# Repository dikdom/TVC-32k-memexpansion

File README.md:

# TVC 32k extender

## Magyar
Ez a repó Videoton TVC 32k bővítő modul terveit tartalmazza. A bővítőmodul arra való, hogy a 32k TVC gép memóriáját +32kB-al, 64k-ra bővítse. 64kB-os TVC gépek memóriáját nem változtatja.

Lehet rá egy LED-et is tenni, de nem muszáj.

Sőt, ha szeretsz tákolni, akkor azt is lehet, hogy ezen a kártyán legyen a TVC új reset gombja is. Sajnos a /RESET jel nincs kivezetve a felső bővítőn (illetve van, csak outputként, kívülről nem lehet a felső bővítőn resetelni a gépet), ezért bogarászni kell gép belsejét és a megfelelő helyre oda kell vinni a lap /RESET jelét. Ha ilyet szeretnél, annak neked kell utánajárnod, hogy hol van az inputnak való /RESET jel a TVC belsejében. A kapcsolási rajzok elérhetőek. 

Mi kell memóriabővítő kártyához:
- 1db 62256 SRAM
- 1db 74LS156 (vagy 74HCT156)
- 2db 100nF, 1# kondenzátor
- 1db 10k, 2# ellenállás
- OPCIONÁLIS
-- 1db 1k, 2# ellenállás, 5mm LED a visszajelzéshez
-- 1db tact kapcsoló, némi drót a külső reset gombhoz
-- foglalatok az ICkhez (DIP-28 6#, DIP-16)

## English
This repository is about a 32kB expansion module for a 32k TVC machine. This board would not change a 64k or 64k+ TVC machine.

Optionally you can attach an LED for checking if the +5V is available in the computer (the PSU when is already warmed up may not turn on again).

Optionally (#2) you can create a new reset switch to the computer, but you have to make your hands dirty in this case. The /RESET line is not exposed on the upper slot, only as an output. If you want to make the TVC reset on the tack switch then you have to route the exposed reset line from the card to the TVC 32k internal RESET line. Where is that point? You have to figure out based on the publicly available schematics of the TVC 32k machines. 

BOM:
- 1x 62256 SRAM
- 1x 74LS156 (or 74HCT156)
- 2x 100nF, 1# capacitors
- 1x 10k 2# resistor
- OPTIONALLY
-- 1x 1k 2# resistor, 5mm LED
-- 1x tact switch, some wire for the extarnal reset
-- sockets for the ICs (DIP-28 6#, DIP-16)

# License: GNU GPL v3

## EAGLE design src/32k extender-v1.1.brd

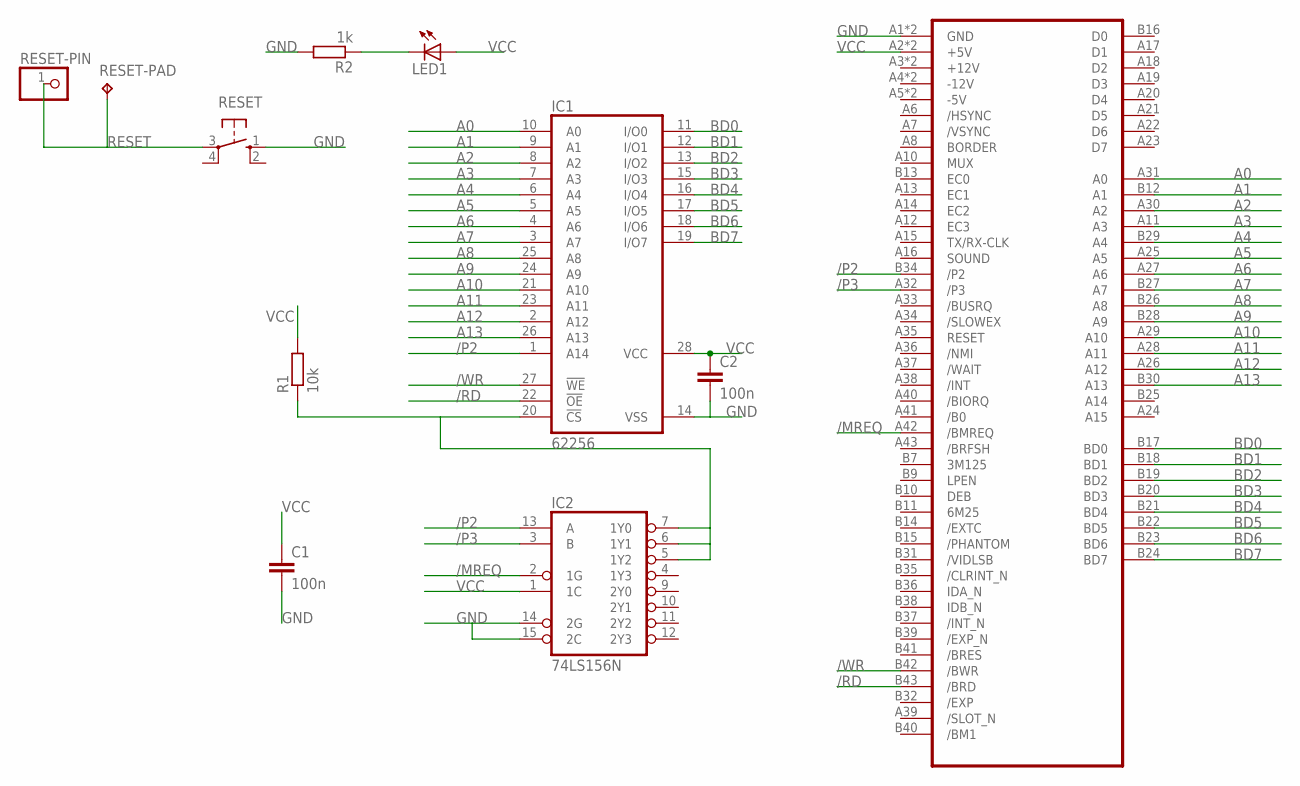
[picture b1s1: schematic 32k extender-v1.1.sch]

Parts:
C1, C2: 100n; C2.5-2
IC1: 62256; DIL28-6
IC2: 74LS156N; DIL16
LED1: LED5MM
R1: 10k; 0204/5
R2: 1k; 0204/5
RESET: 10-XX; B3F-10XX
RESET-PAD: TPTP13SQ; TP13SQ
RESET-PIN: PINHD-1X1; 1X01
U$1: TVC-EXP-HBA; TVC-EXP-EDGE

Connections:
/MREQ: IC2.2 (1G), U$1.A42 (/BMREQ)
/P2: IC1.1 (A14), IC2.13 (A), U$1.B34 (/P2)
/P3: IC2.3 (B), U$1.A32 (/P3)
/RD: IC1.22 (!OE), U$1.B43 (/BRD)
/WR: IC1.27 (!WE), U$1.B42 (/BWR)
A0: IC1.10 (A0), U$1.A31 (A0)
A1: IC1.9 (A1), U$1.B12 (A1)
A2: IC1.8 (A2), U$1.A30 (A2)
A3: IC1.7 (A3), U$1.A11 (A3)
A4: IC1.6 (A4), U$1.B29 (A4)
A5: IC1.5 (A5), U$1.A25 (A5)
A6: IC1.4 (A6), U$1.A27 (A6)
A7: IC1.3 (A7), U$1.B27 (A7)
A8: IC1.25 (A8), U$1.B26 (A8)
A9: IC1.24 (A9), U$1.B28 (A9)
A10: IC1.21 (A10), U$1.A29 (A10)
A11: IC1.23 (A11), U$1.A28 (A11)
A12: IC1.2 (A12), U$1.A26 (A12)
A13: IC1.26 (A13), U$1.B30 (A13)
BD0: IC1.11 (I/O0), U$1.B17 (BD0)
BD1: IC1.12 (I/O1), U$1.B18 (BD1)
BD2: IC1.13 (I/O2), U$1.B19 (BD2)
BD3: IC1.15 (I/O3), U$1.B20 (BD3)
BD4: IC1.16 (I/O4), U$1.B21 (BD4)
BD5: IC1.17 (I/O5), U$1.B22 (BD5)
BD6: IC1.18 (I/O6), U$1.B23 (BD6)
BD7: IC1.19 (I/O7), U$1.B24 (BD7)
GND: C1.2, C2.2, IC1.14 (VSS), IC2.8 (GND), IC2.14 (2G), IC2.15 (2C), R2.2, RESET.1 (S), U$1.A1 (GND), U$1.B1 (GND)
unnamed: IC1.20 (!CS), IC2.5 (1Y2), IC2.6 (1Y1), IC2.7 (1Y0), R1.1
unnamed: LED1.K (C), R2.1
RESET: RESET.3, RESET-PAD.TP, RESET-PIN.1
VCC: C1.1, C2.1, IC1.28 (VCC), IC2.1 (1C), IC2.16 (VCC), LED1.A, R1.2, U$1.A2 (+5V), U$1.B2 (+5V)

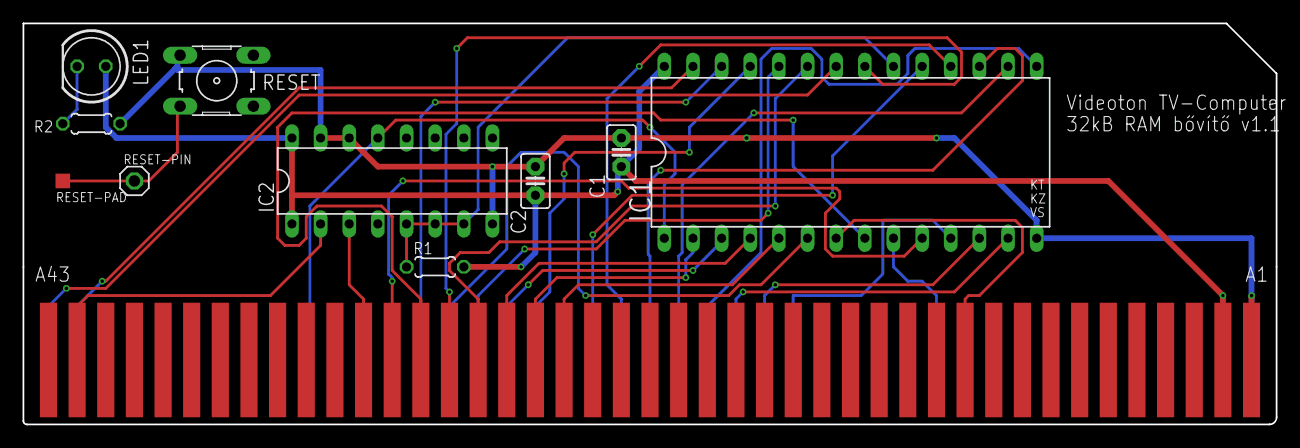
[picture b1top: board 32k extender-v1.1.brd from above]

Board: 2 copper layers, 111.1 x 35.6 mm, 11 parts (0 on the bottom side), 32 nets.

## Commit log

2021-04-10 Update README.md
    Paragraph ends...
2021-11-07 gerber files
    The gerber files of the 32k memory expansion of the TVC
